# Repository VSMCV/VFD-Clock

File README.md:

# VFD-Clock
hardware design and software files for a vacuum fluorescent display clock

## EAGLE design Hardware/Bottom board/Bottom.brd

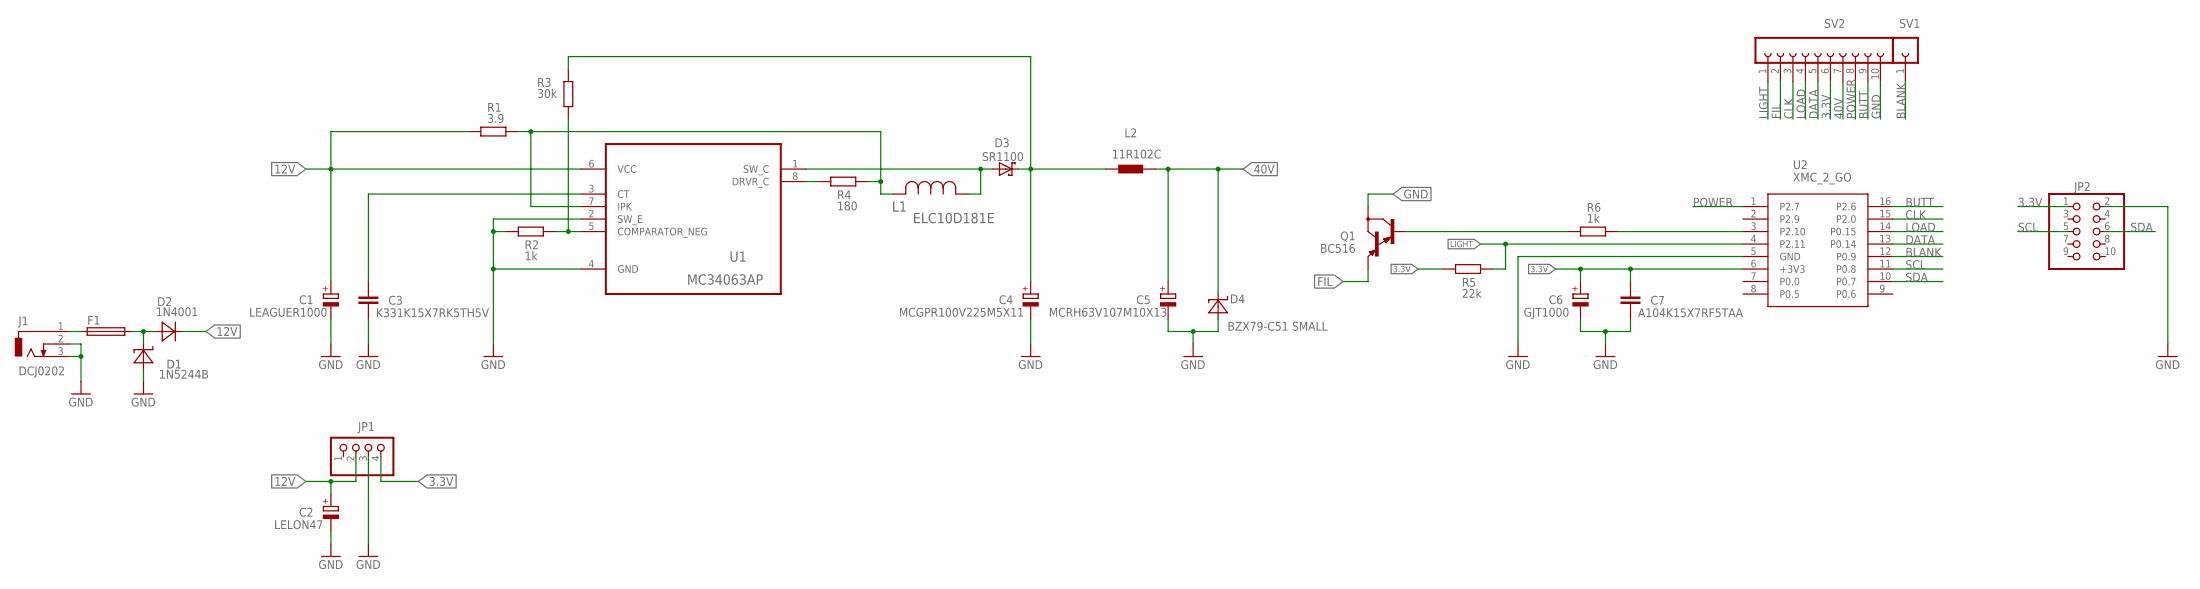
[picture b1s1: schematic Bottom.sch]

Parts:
C1: LEAGUER1000; E5-10
C2: LELON47; E2,5-6
C3: K331K15X7RK5TH5V; C025-025X050
C4: MCGPR100V225M5X11; E2,5-5
C5: MCRH63V107M10X13; E5-10
C6: GJT1000; E2,5-8
C7: A104K15X7RF5TAA; C025-025X050
D1: 1N5244B; DO41-7
D2: 1N4001; DO41-7
D3: SR1100; DO41-7
D4: BZX79-C51 SMALL; DO35-7
F1: SH22,5
J1: DCJ0202
JP1: PINHD-1X4; 1X04
JP2: PINHD-2X5/90; 2X05/90
L1: ELC10D181E; IND_ELC10D
L2: 11R102C; L2,5-5
Q1: BC516; TO92
R1: 3.9; 0207/10
R2, R6: 1k; 0207/10
R3: 30k; 0207/10
R4: 180; 0207/10
R5: 22k; 0207/10
SV1: FE01; FE05-1
SV2: FE10-1; FE10
U1: MC34063AP; DIP254P762X508-8
U2: XMC_2_GO

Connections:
3.3V: C6.+, C7.1, JP1.4, JP2.1, R5.1, SV2.6, U2.6 (+3V3)
5V: L1.2, R1.2, R4.2, U1.7 (IPK)
12V: C1.+, C2.+, D2.C, JP1.2, R1.1, U1.6 (VCC)
40V: C5.+, D4.C, L2.2, SV2.7
BLANK: SV1.1, U2.12 (P0.9)
BUTT: SV2.9, U2.16 (P2.6)
CLK: SV2.3, U2.15 (P2.0)
DATA: SV2.5, U2.13 (P0.14)
FIL: Q1.1 (E), SV2.2
GND: C1.-, C2.-, C3.2, C4.-, C5.-, C6.-, C7.2, D1.A, D4.A, J1.2, J1.3, JP1.3, JP2.2, Q1.3 (C), R2.1, SV2.10, U1.2 (SW_E), U1.4 (GND), U2.5 (GND)
LIGHT: R5.2, SV2.1, U2.4 (P2.11)
LOAD: SV2.4, U2.14 (P0.15)
unnamed: Q1.2 (B), R6.1
unnamed: R6.2, U2.3 (P2.10)
unnamed: F1.1, J1.1
unnamed: C4.+, D3.C, L2.1, R3.1
unnamed: C3.1, U1.3 (CT)
unnamed: R2.2, R3.2, U1.5 (COMPARATOR_NEG)
unnamed: D3.A, L1.1, U1.1 (SW_C)
unnamed: R4.1, U1.8 (DRVR_C)
POW: D1.C, D2.A, F1.2
POWER: SV2.8, U2.1 (P2.7)
SCL: JP2.5, U2.11 (P0.8)
SDA: JP2.6, U2.10 (P0.7)

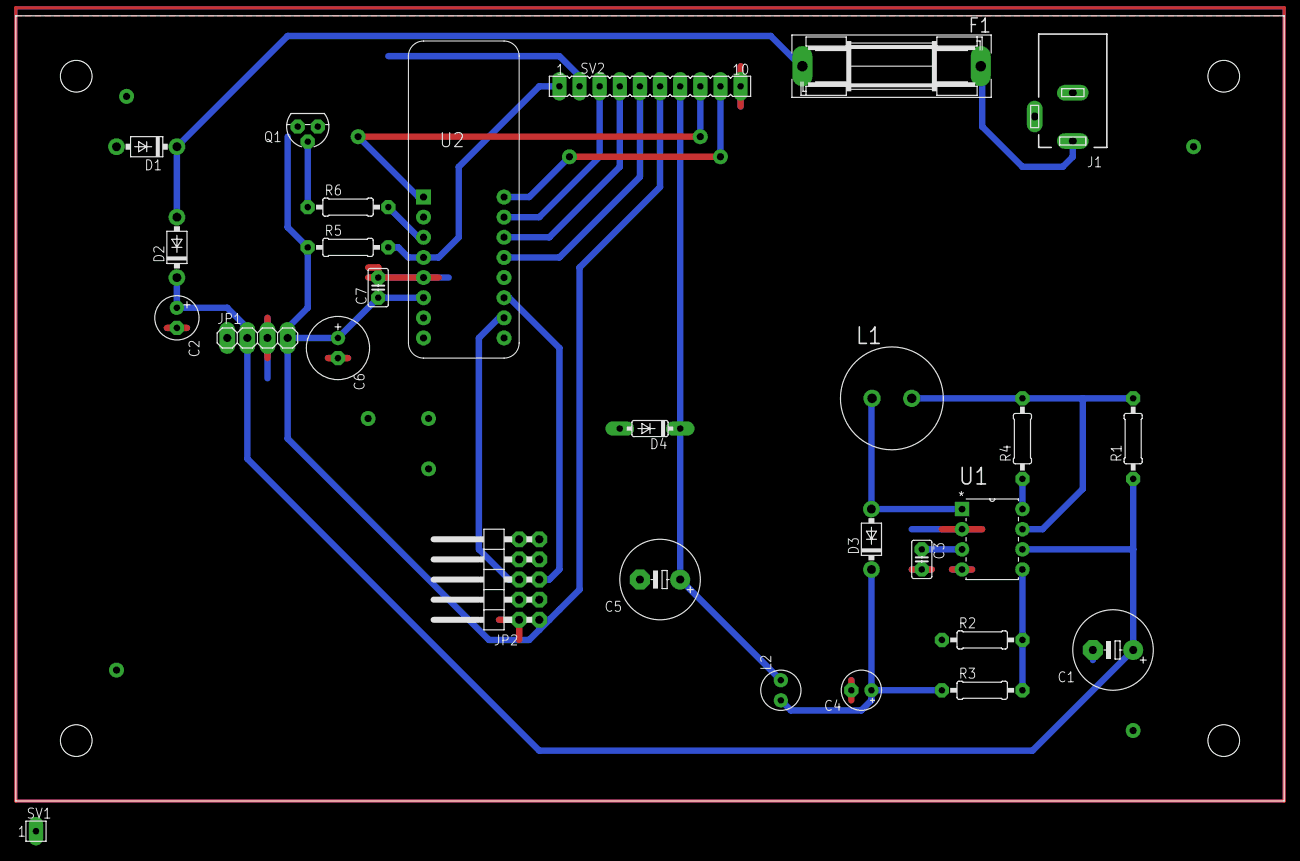
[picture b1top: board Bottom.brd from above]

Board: 2 copper layers, 160.0 x 99.1 mm, 28 parts (0 on the bottom side), 24 nets.

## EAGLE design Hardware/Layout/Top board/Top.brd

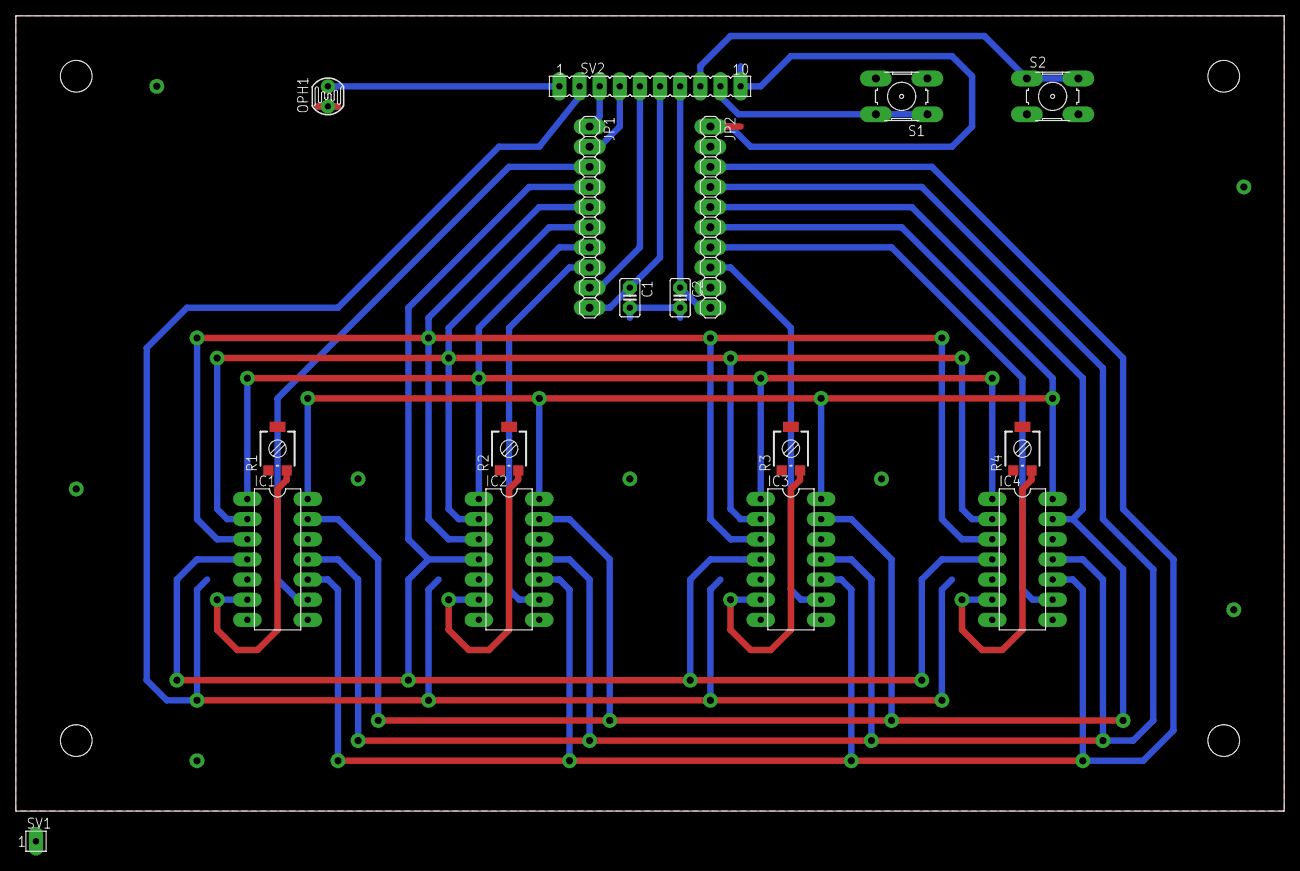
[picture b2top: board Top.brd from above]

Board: 2 copper layers, 160.0 x 100.3 mm, 17 parts (0 on the bottom side), 27 nets.

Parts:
C1, C2: A104K15X7RF5TAA; C025-025X050
IC1, IC2, IC3, IC4: IV-6; DIL14
JP1, JP2: 1X10
OPH1: VT93N3; VT900
R1, R2, R3, R4: 20; RTRIM3314G
S1, S2: 3314G-1-200E; B3F-10XX
SV1: FE05-1
SV2: FE10

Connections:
3.3V: C1.1, IC1.5, IC2.5, IC3.5, IC4.5, JP1.10, SV2.6
40V: C2.1, JP2.10, SV2.7
A: IC1.14, IC2.14, IC3.14, IC4.14, JP2.6
B: IC1.2, IC2.2, IC3.2, IC4.2, JP1.6
BLANK: JP2.2, SV1.1
BUTT: S1.1, S1.2, SV2.9
C: IC1.13, IC2.13, IC3.13, IC4.13, JP2.5
CLK: JP1.1, SV2.3
D: IC1.1, IC2.1, IC3.1, IC4.1, JP1.7
DATA: JP1.9, SV2.5
E: IC1.3, IC2.3, IC3.3, IC4.3, JP1.5
F: IC1.10, IC2.10, IC3.10, IC4.10, JP2.3
FIL: R1.2, R2.2, R3.2, R4.2, SV2.2
G: IC1.4, IC2.4, IC3.4, IC4.4, JP1.4
GND: C1.2, C2.2, JP2.1, OPH1.2, S1.3, S1.4, S2.3, S2.4, SV2.10
GR0: IC1.9, JP1.3
GR1: IC2.9, JP1.8
GR2: IC3.9, JP2.8
GR3: IC4.9, JP2.7
H: IC1.11, IC2.11, IC3.11, IC4.11, JP2.4
LIGHT: OPH1.1, SV2.1
LOAD: JP1.2, SV2.4
unnamed: IC1.6, R1.1
unnamed: IC2.6, R2.1
unnamed: IC3.6, R3.1
unnamed: IC4.6, R4.1
POWER: S2.1, S2.2, SV2.8

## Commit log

2017-09-04 initial
2017-09-04 reorganized stuff
2019-01-11 Add bottom schematic pic
2019-01-11 Add top schematic pic
2019-01-11 Add bottom layout pic
2019-01-11 Add top layout pic
